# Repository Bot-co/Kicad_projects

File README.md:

# 🔌 Custom ATtiny85 USB Development Board

A compact USB-powered development board built around the **ATtiny85-20S** microcontroller.  
The design includes USB data-line protection, an onboard LED, decoupling capacitor, and two GPIO header connectors for easy prototyping.

This is my own minimal version of a Digispark-style board, fully designed in **KiCad** from scratch.

---

## 📌 Features

- **Microcontroller:** ATtiny85-20S (SOIC-8)
- **USB Interface:** Direct USB pads on PCB  
  - Zener-diode protection on D+ / D−  
  - 1.5k USB pull-up resistor
- **Power:** 5V from USB
- **I/O:**  
  - Header **J1** (PB0, PB1, PB2, PB3)  
  - Header **J2** (PB4, PB5, GND, VCC)
- **Onboard LED:** Connected to PB0 (via R3 330Ω)
- **Decoupling capacitor:** 100nF near VCC
- **Compact PCB layout with USB edge connector**

---

## 🛠 Schematic Overview

Key components used:

| Component | Function |
|----------|----------|
| ATtiny85-20S | Main microcontroller |
| C1 100nF | Power supply decoupling |
| D1, D2 (3.6V Zener) | USB D+ / D− protection |
| R4 1.5k | USB pull-up (D+) |
| R1, R2 (68Ω) | USB D+ / D− series resistors |
| R3 330Ω | LED current limiting |
| D3 LED | Status indicator |
| J1 / J2 | Expansion headers |

USB pads route directly to D+ and D− via the standard Digispark-style resistor/zener configuration.

---

## 📐 PCB

The PCB is designed to plug directly into a USB Type-A port.  
Major layout highlights:

- Short trace routing for USB lines  
- Zener diodes placed close to USB pads  
- Decoupling capacitor placed near ATtiny VCC pin  
- LED positioned on the top side for visibility  
- Two 4-pin headers (J1 and J2) for GPIO access  
- Clean ground plane and simple 2-layer routing

Renders are available in `/docs/`:

- `top.png`  
- `bottom.png`

(You can export your own and place them here.)

---

## 🔌 Pinout

| Pin | ATtiny85 Function | Connected To |
|-----|--------------------|--------------|
| PB0 | I/O / PWM | LED (via R3) + J1 |
| PB1 | I/O | J1 |
| PB2 | I/O | J1 |
| PB3 | I/O | J1 |
| PB4 | I/O | J2 |
| PB5 | RESET / I/O | J2 |
| VCC | 5V | USB VBUS |
| GND | Ground | USB GND |

---

## 💾 Programming

This board uses the ATtiny85-20S, which supports:

- **USBasp**
- **Arduino as ISP**
- **AVRDUDE**
- **Micronucleus bootloader**

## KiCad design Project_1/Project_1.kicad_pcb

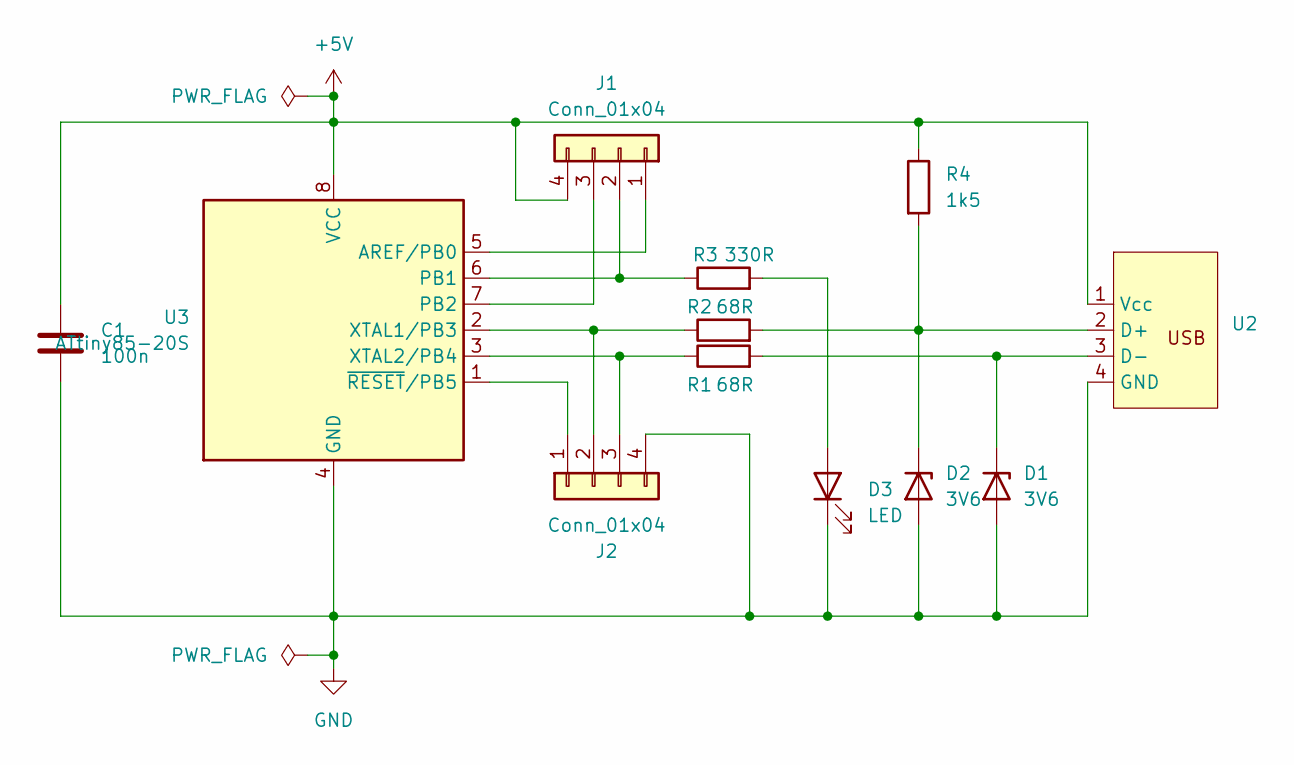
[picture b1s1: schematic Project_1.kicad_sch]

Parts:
C1: 100n; C_1206_3216Metric_Pad1.33x1.80mm_HandSolder
D1, D2: 3V6; D_SOD-123
D3: LED; LED_D3.0mm
J1, J2: Conn_01x04; PinHeader_1x04_P2.54mm_Vertical
R1, R2: 68R; R_0805_2012Metric_Pad1.20x1.40mm_HandSolder
R3: 330R; R_0805_2012Metric_Pad1.20x1.40mm_HandSolder
R4: 1k5; R_0805_2012Metric_Pad1.20x1.40mm_HandSolder
U2: PCB_USB_connector
U3: ATtiny85-20S; SOIC-8_5.3x5.3mm_P1.27mm

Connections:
+5V: C1.1, J1.4, R4.1, U2.1 (Vcc), U3.8 (VCC)
GND: C1.2, D1.2 (A), D2.2 (A), D3.1 (K), J2.4, U2.4 (GND), U3.4 (GND)
unnamed: D1.1 (K), R1.2, U2.3 (D-)
unnamed: D2.1 (K), R2.2, R4.2, U2.2 (D+)
unnamed: D3.2 (A), R3.2
unnamed: J1.1, U3.5 (AREF/PB0)
unnamed: J1.2, R3.1, U3.6 (PB1)
unnamed: J1.3, U3.7 (PB2)
unnamed: J2.1, U3.1 (~RESET/PB5)
unnamed: J2.2, R2.1, U3.2 (XTAL1/PB3)
unnamed: J2.3, R1.1, U3.3 (XTAL2/PB4)

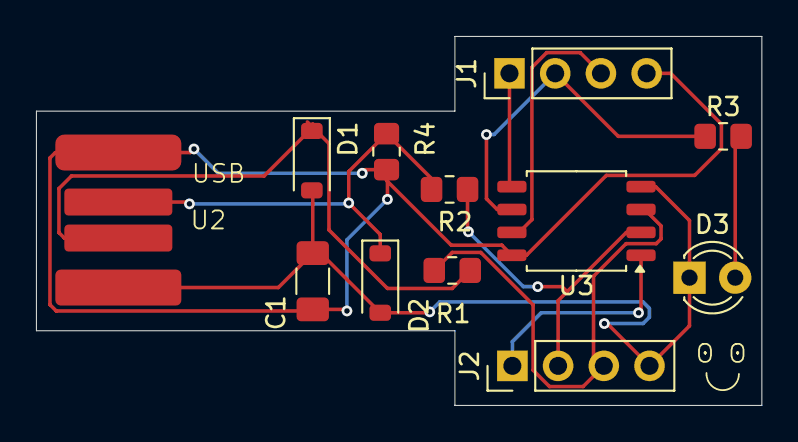
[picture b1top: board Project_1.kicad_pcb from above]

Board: 2 copper layers, 40.3 x 20.5 mm, 12 parts (0 on the bottom side), 11 nets.

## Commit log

2025-11-17 version_1
2025-11-17 Detailed readme
2025-11-17 readme file
